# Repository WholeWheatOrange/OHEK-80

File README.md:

# OHEK-80
An analog hall effect keyboard using [Void Switches](https://github.com/riskable/void_switch) in the traditional 87-key tenkeyless layout.

# Roadmap
## Under Development
- PCB
## Planned Features
- Analog input
- Adjustable actuation point
- Rapid Trigger
- SOCD
- That Stupid Strap Attachment That Is A Trend In Hall Effect Keyboards

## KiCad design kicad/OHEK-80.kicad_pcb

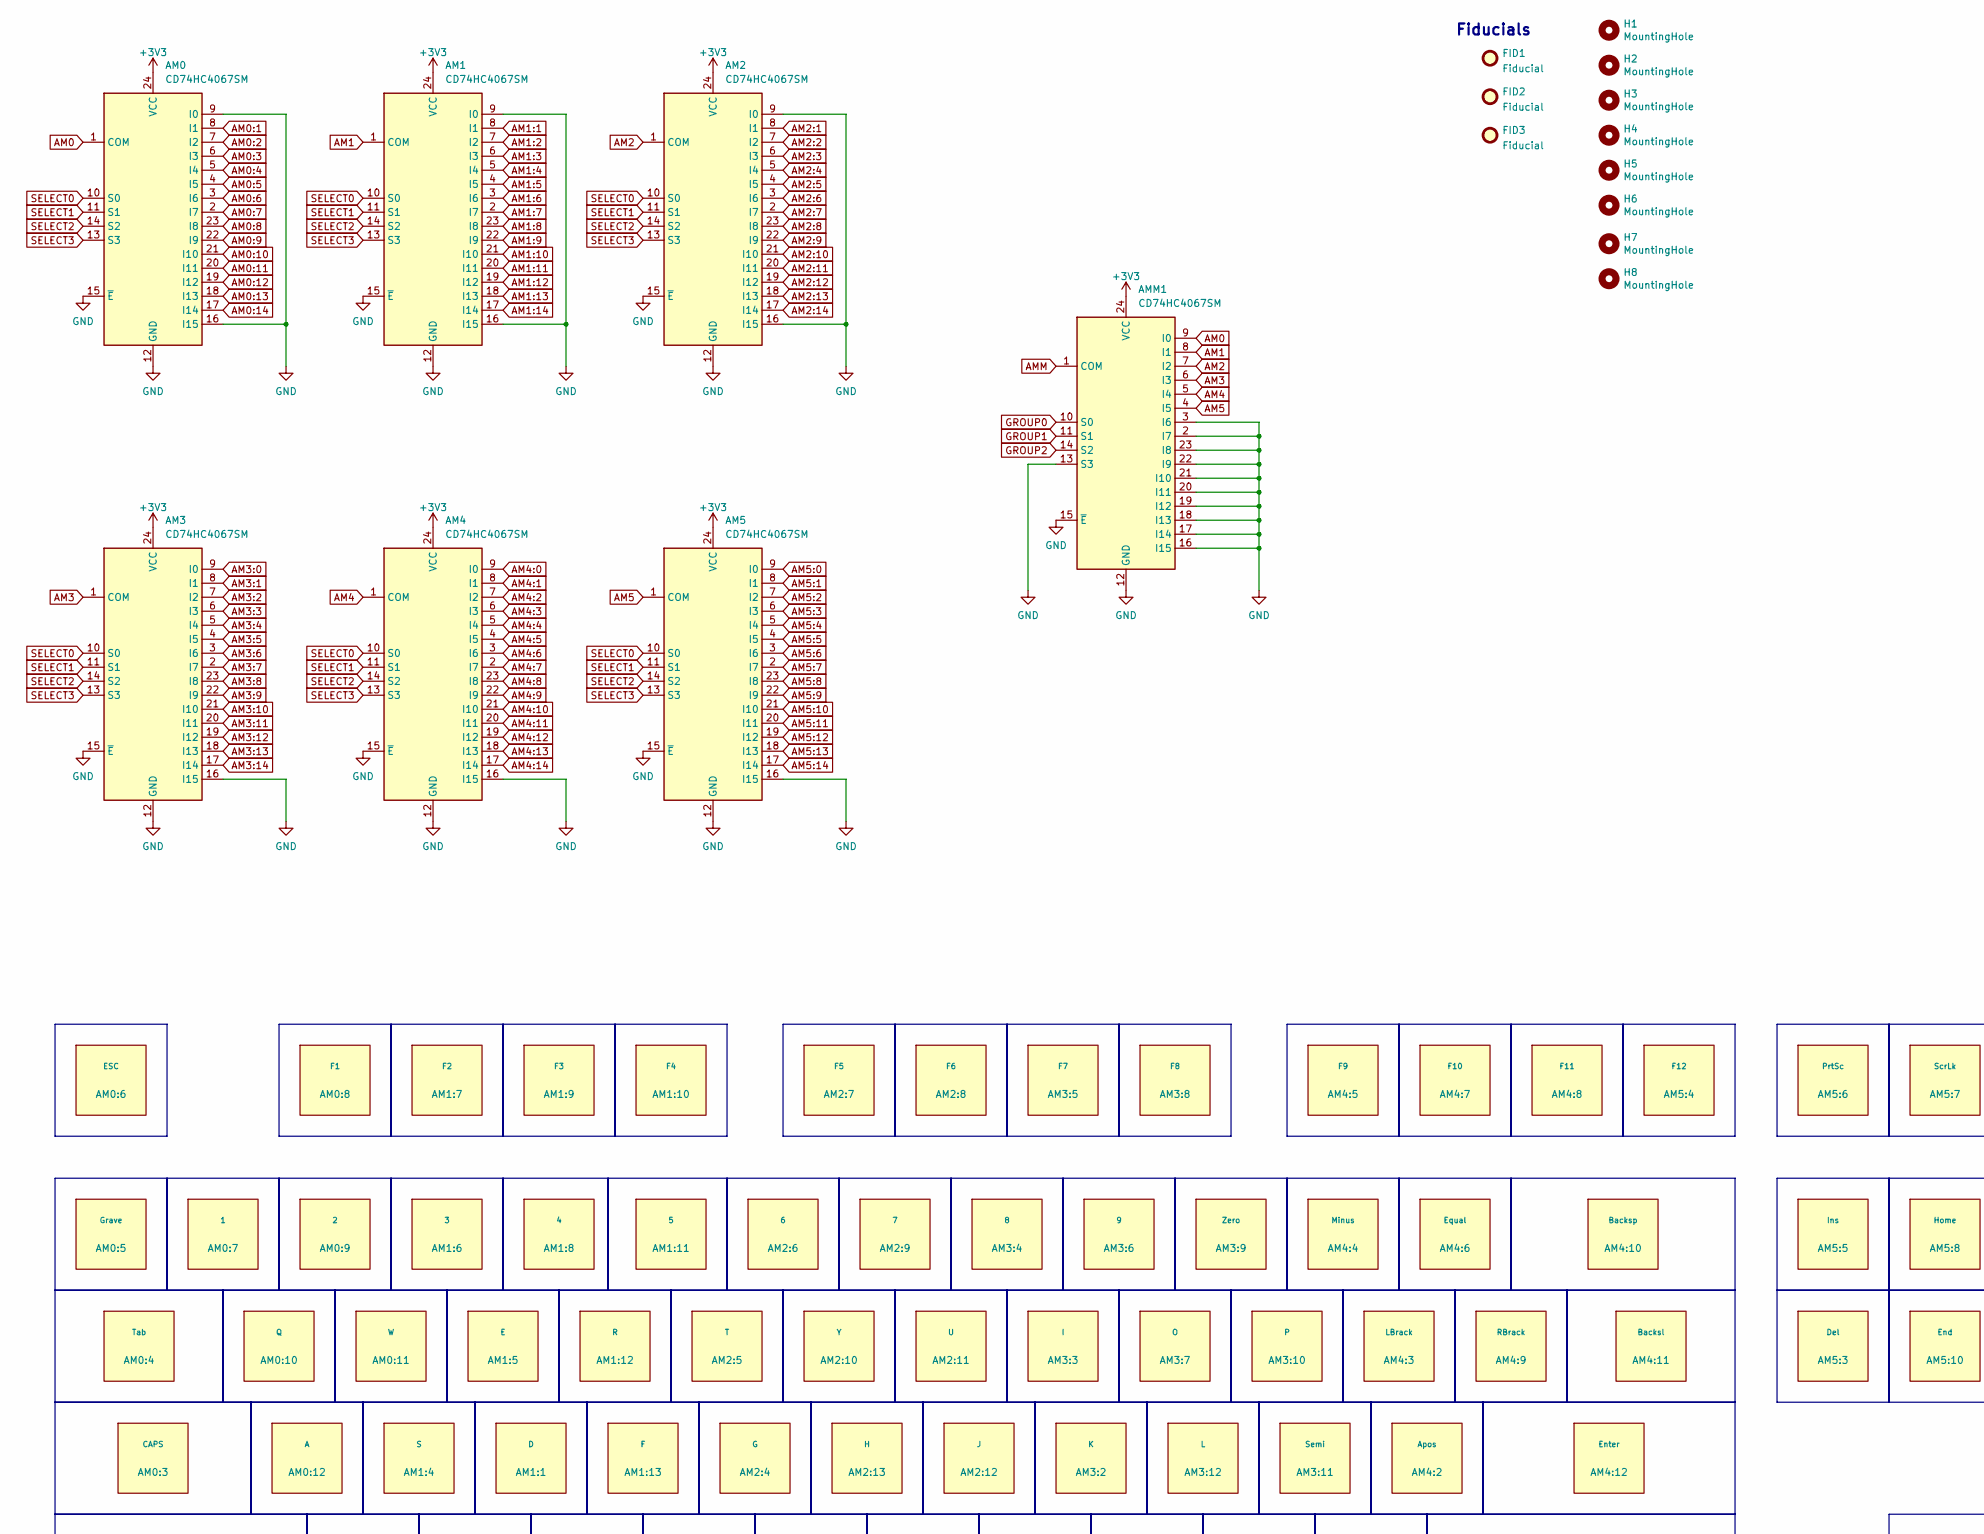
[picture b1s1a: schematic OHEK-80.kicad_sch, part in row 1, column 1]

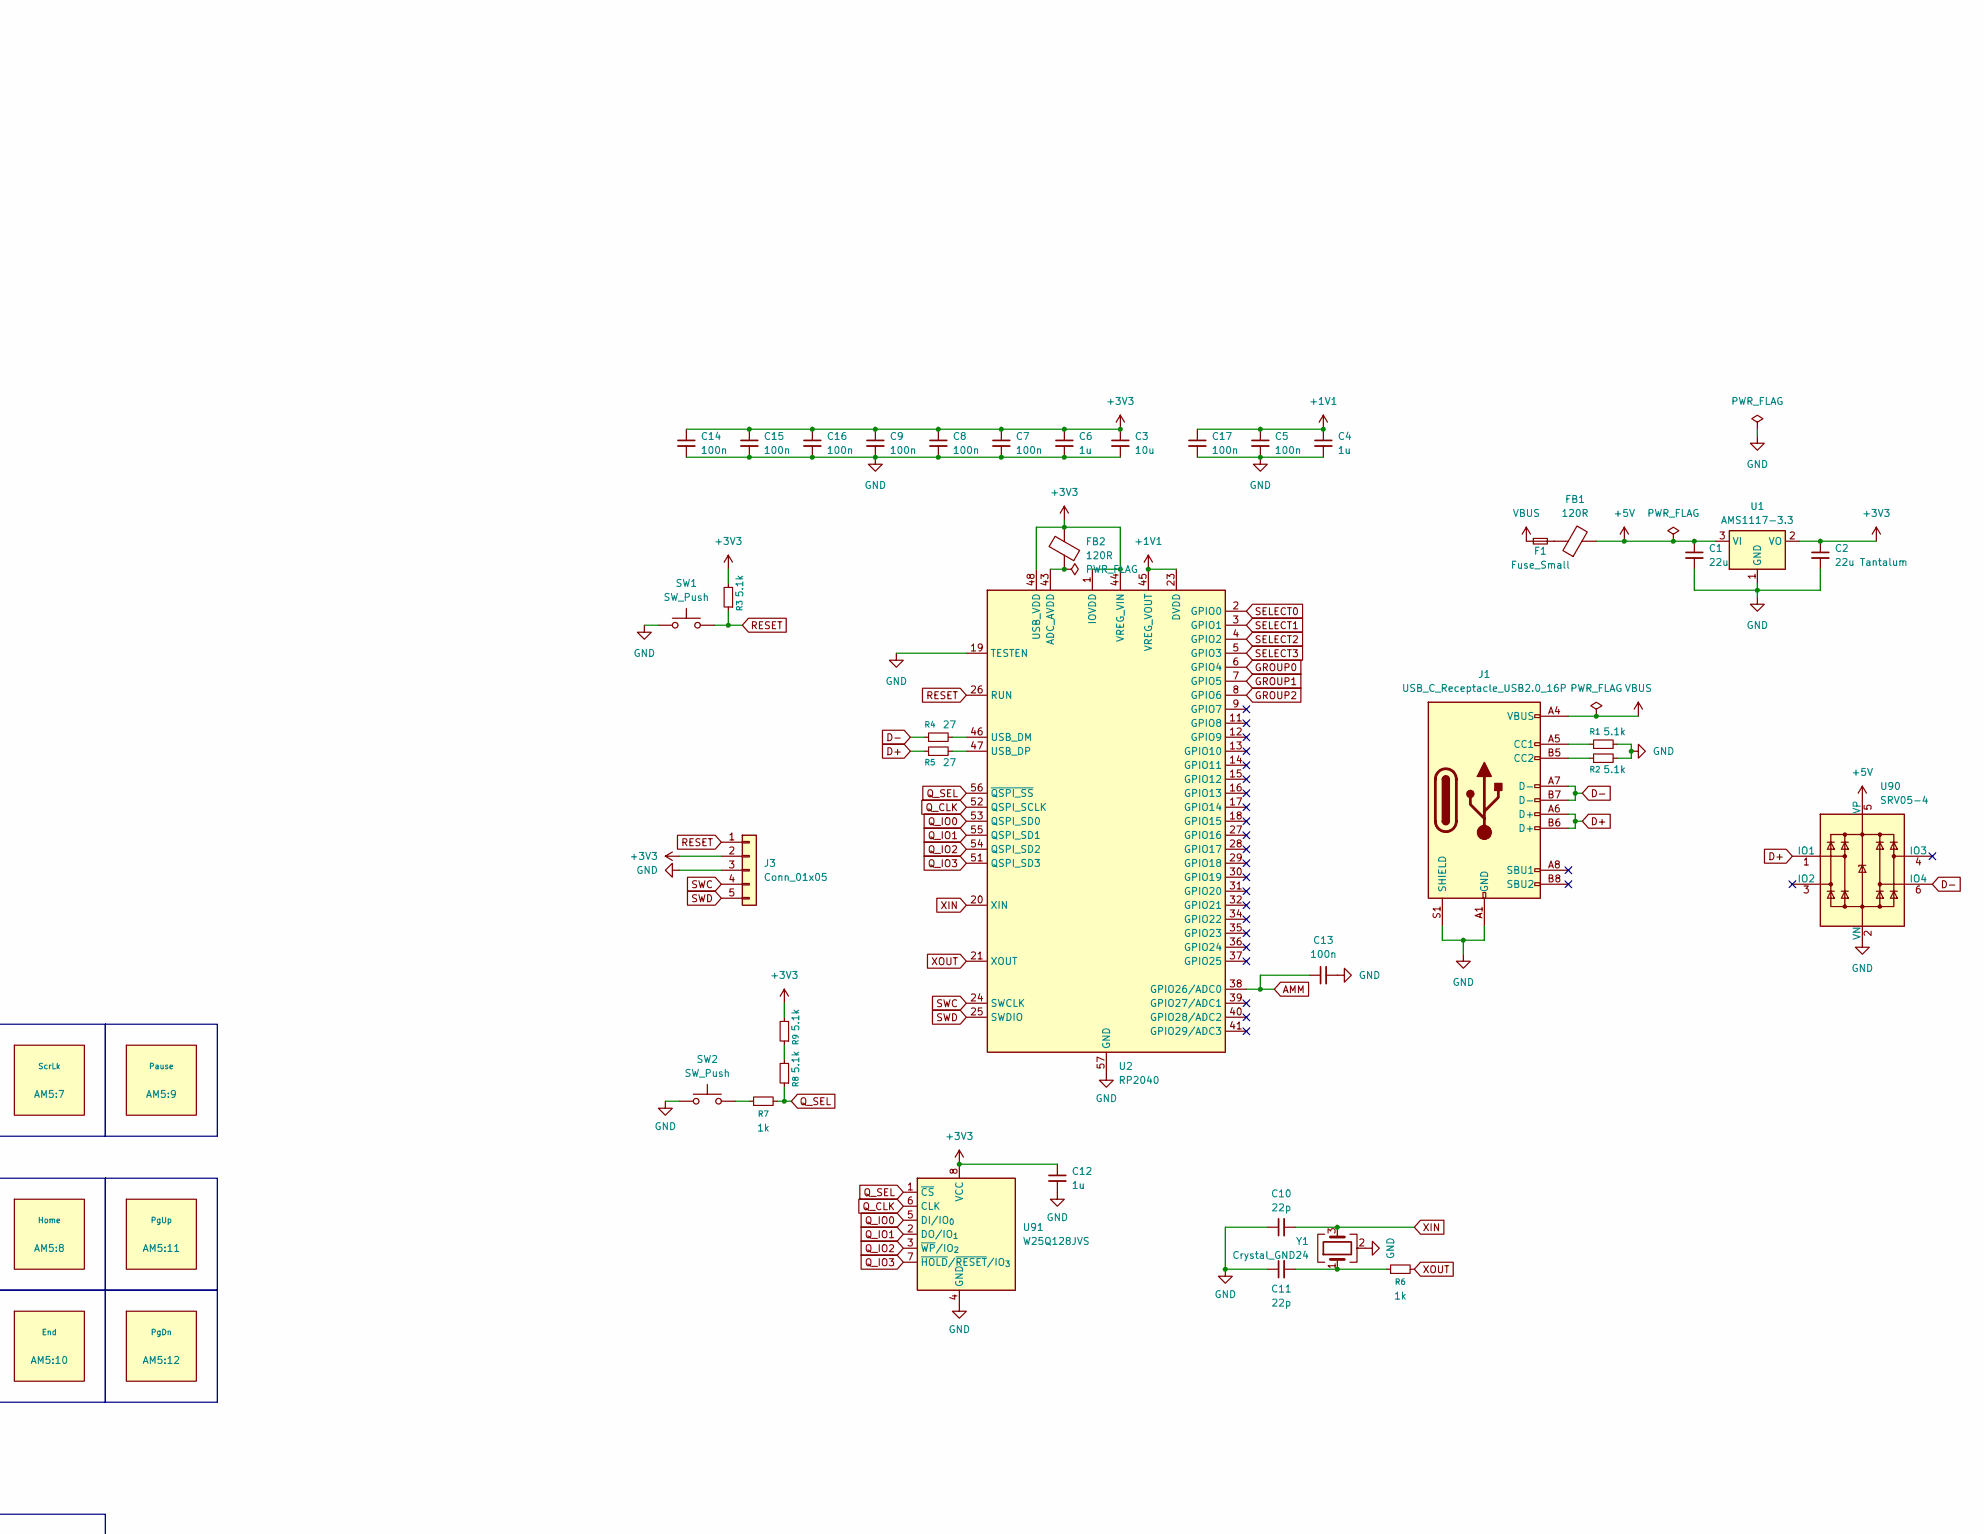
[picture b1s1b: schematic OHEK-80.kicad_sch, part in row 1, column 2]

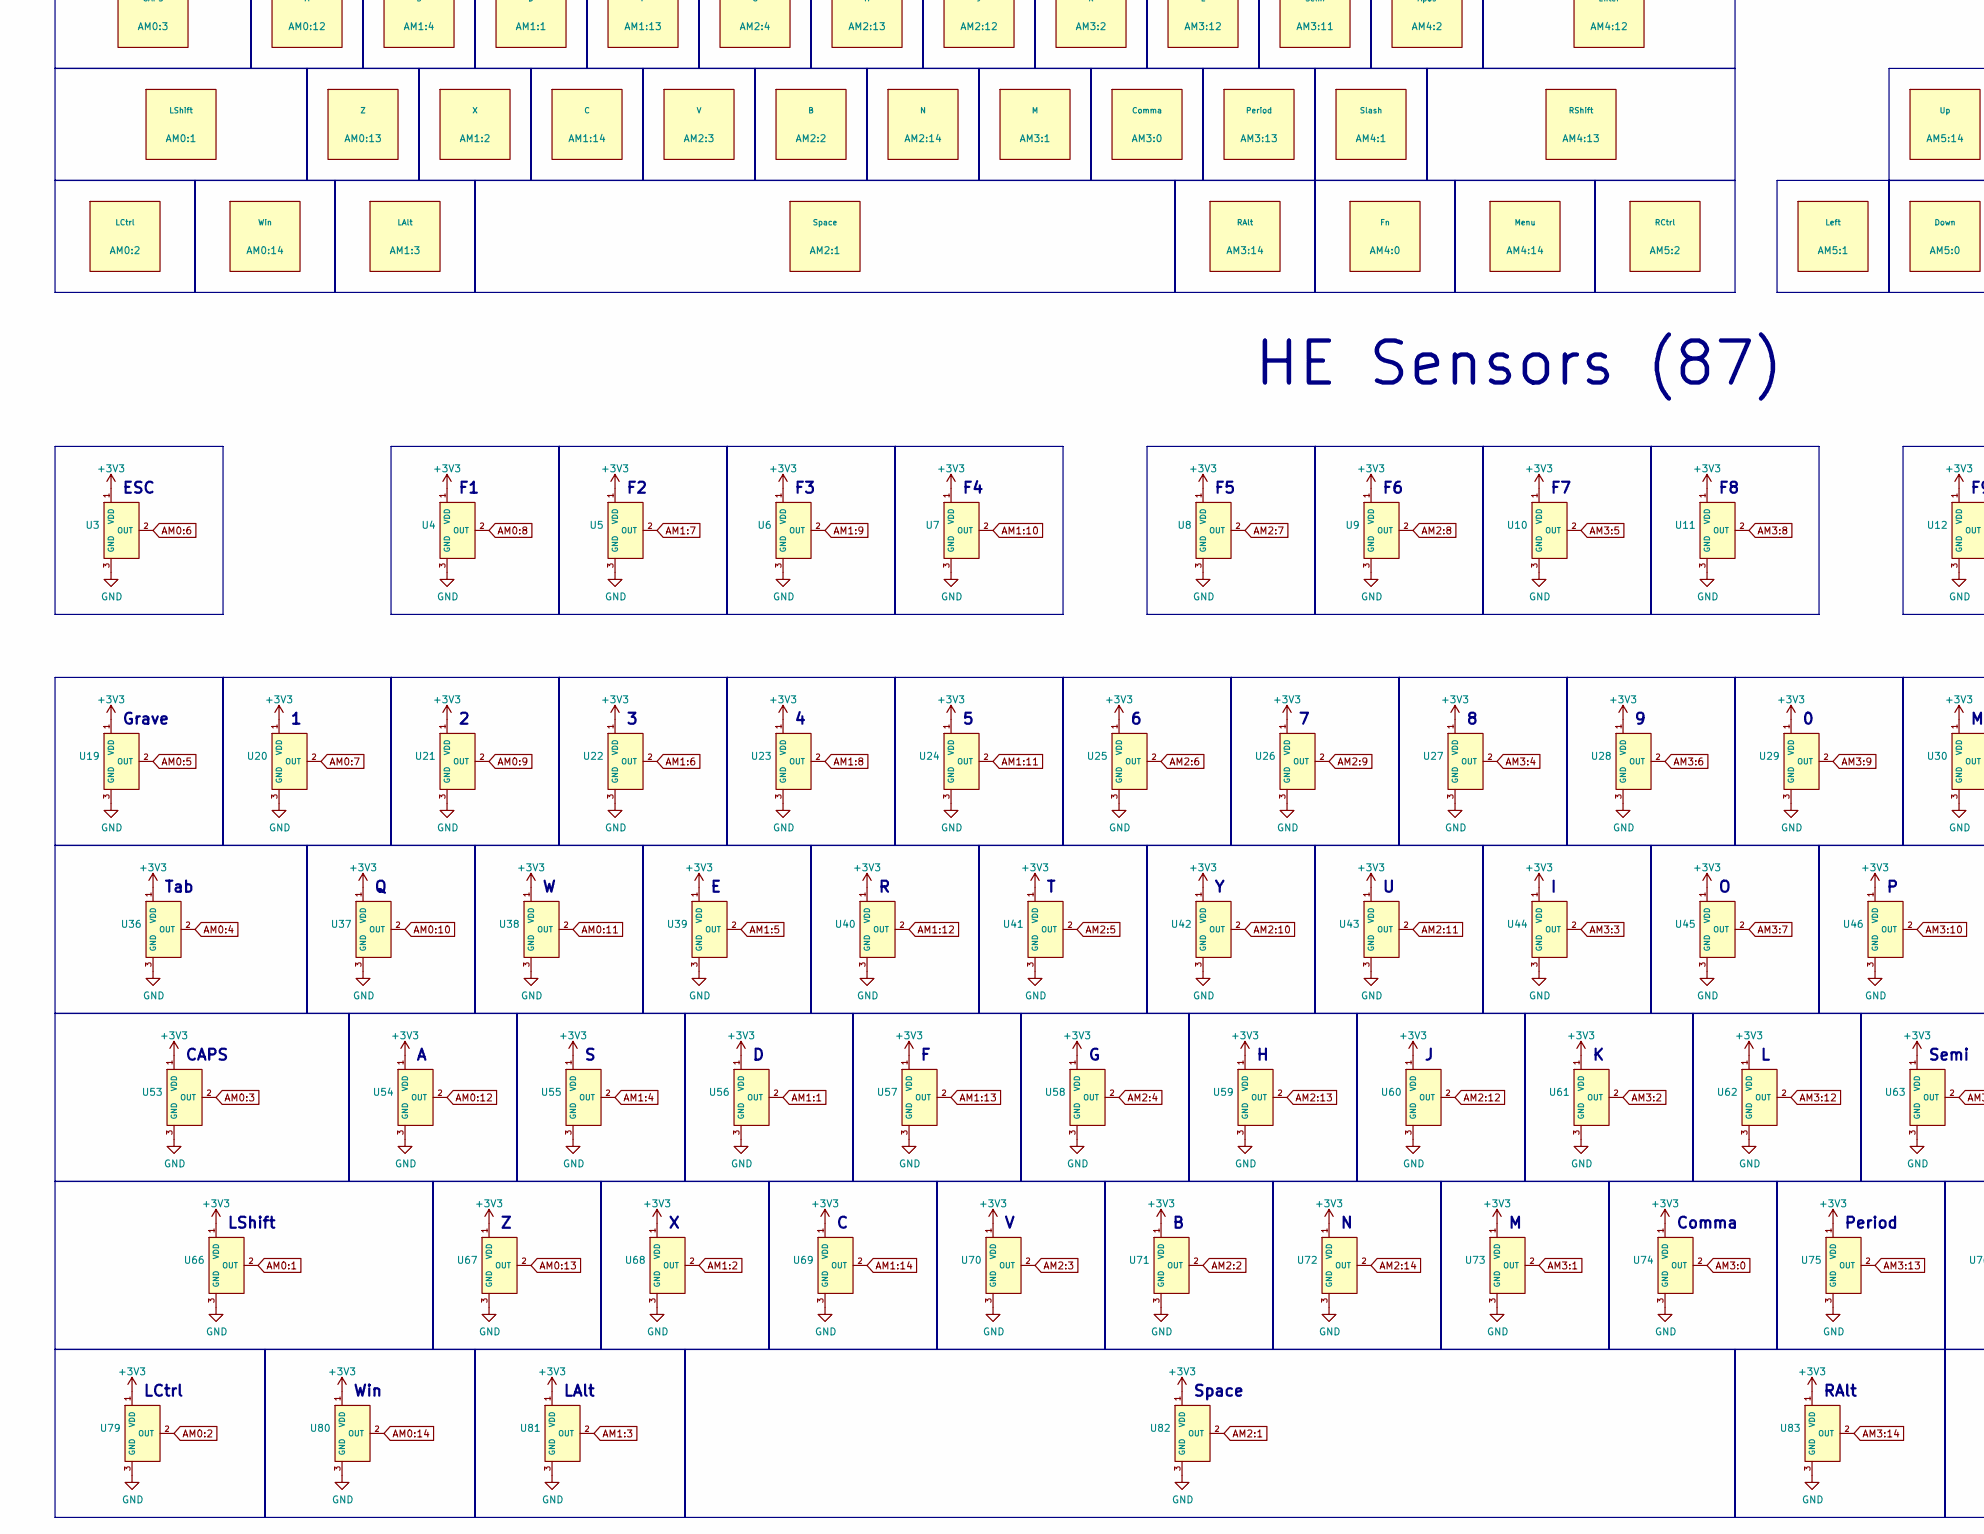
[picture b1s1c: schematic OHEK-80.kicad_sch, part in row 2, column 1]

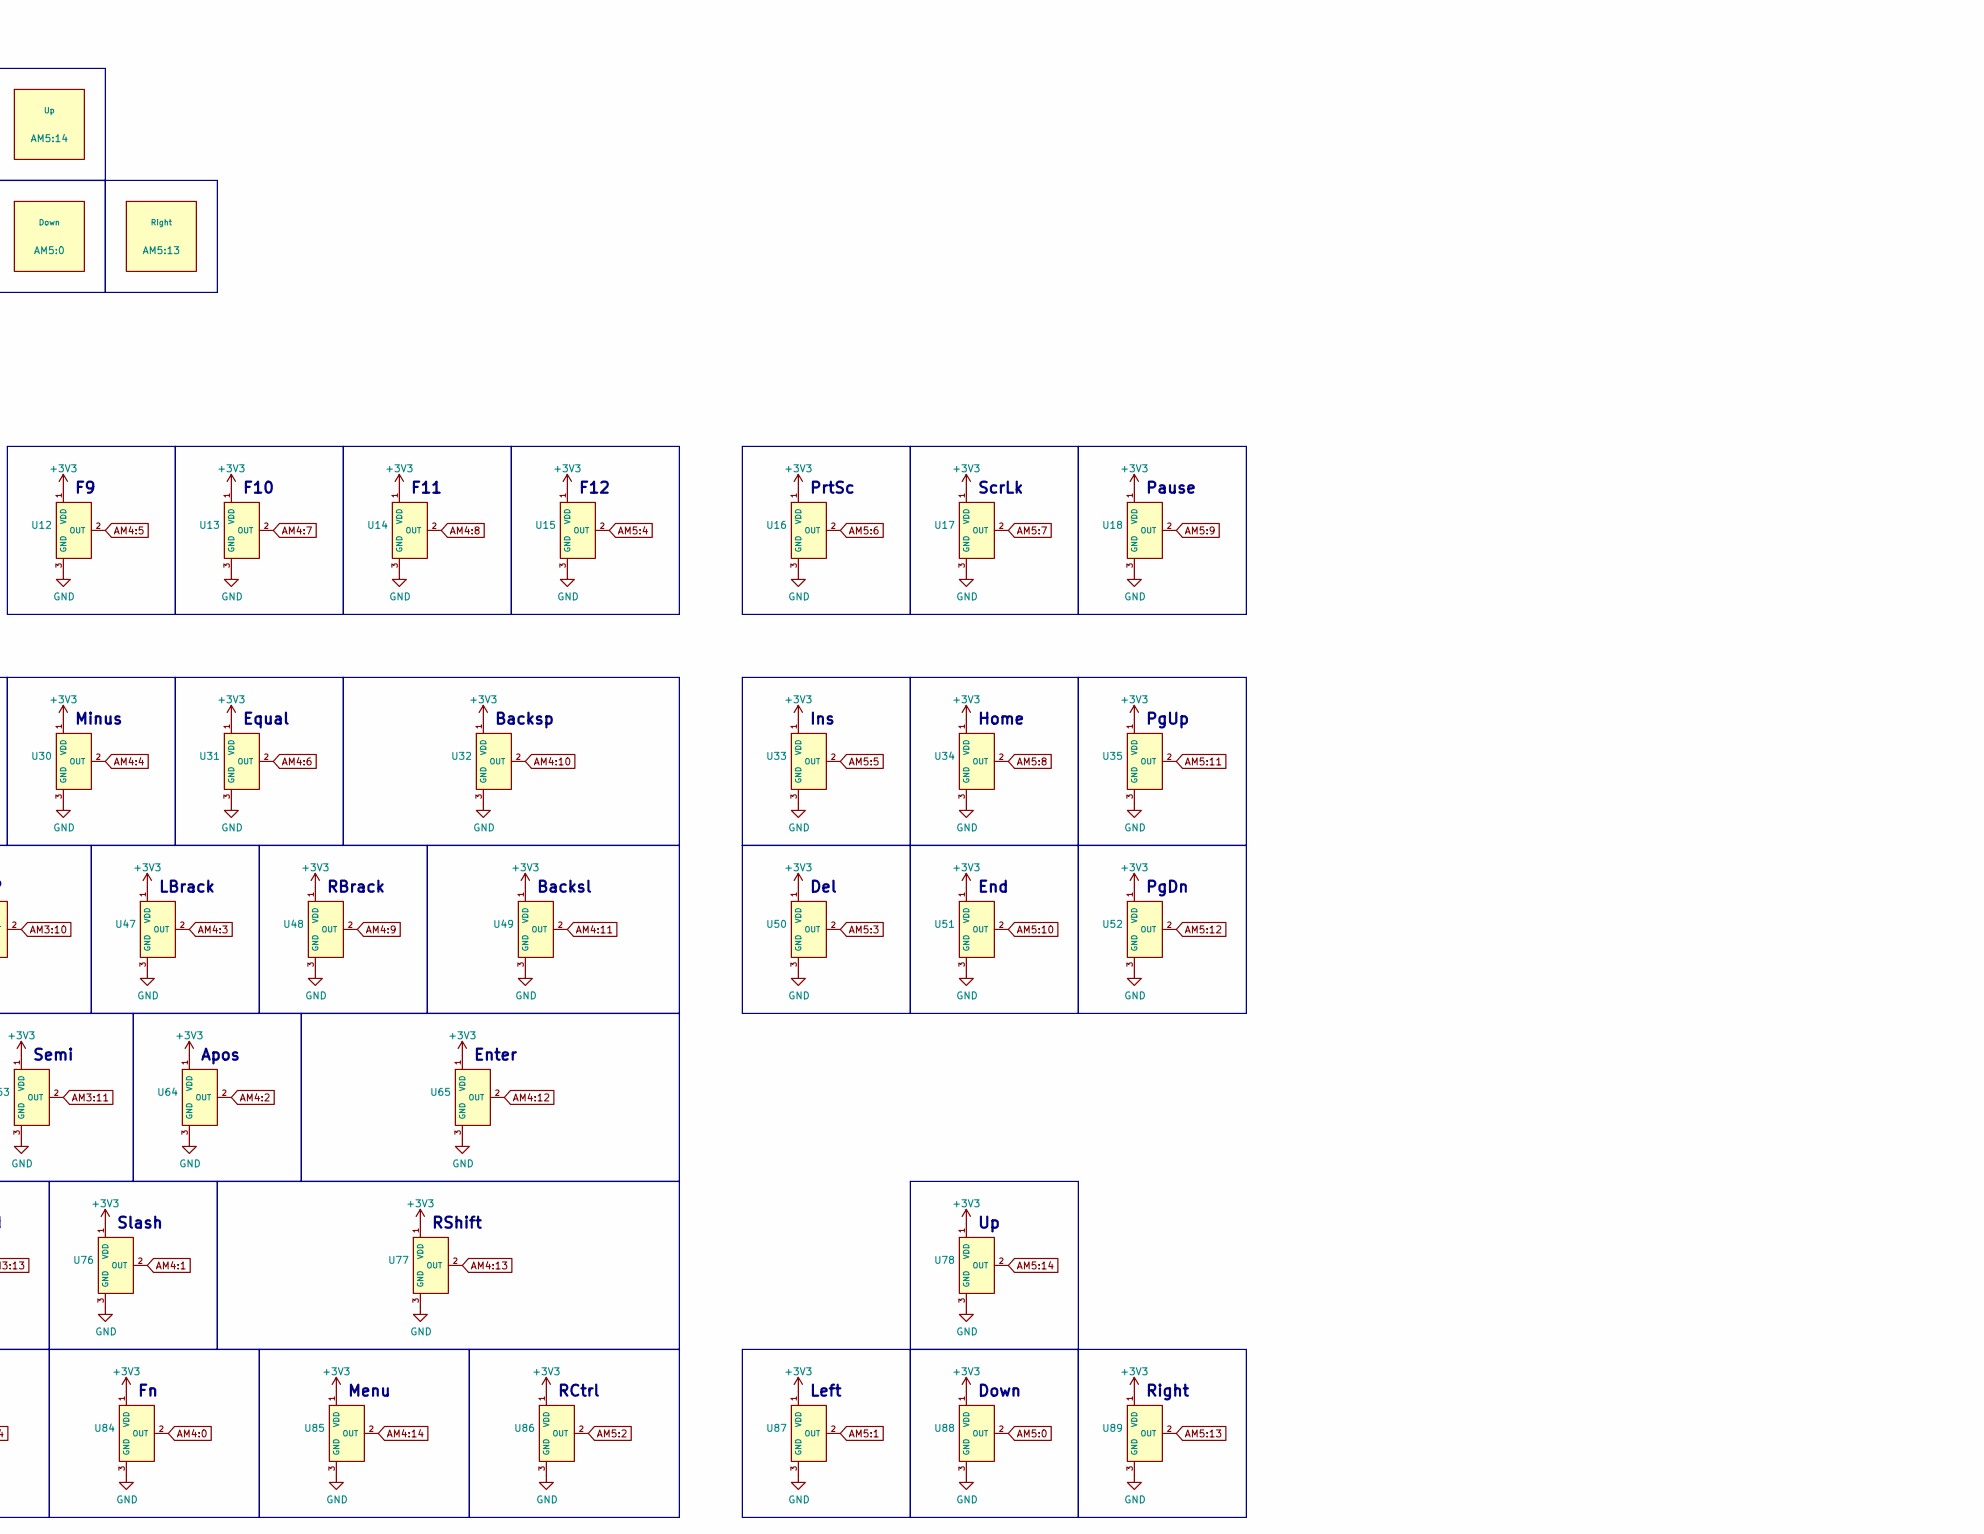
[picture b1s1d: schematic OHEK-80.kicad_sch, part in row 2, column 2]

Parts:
AM0, AM1, AM2, AM3, AM4, AM5: CD74HC4067SM; SSOP-24_5.3x8.2mm_P0.65mm; LCSC C98457
AM0:1: LShift; VoidSwitch_2.25u_SMD
AM0:2: LCtrl; VoidSwitch_1.25u_SMD
AM0:3: CAPS; VoidSwitch_1.75u_SMD
AM0:4: Tab; VoidSwitch_1.5u_SMD
AM0:5: Grave; VoidSwitch_1u_SMD
AM0:6: ESC; VoidSwitch_1u_SMD
AM0:7: 1; VoidSwitch_1u_SMD
AM0:8: F1; VoidSwitch_1u_SMD
AM0:9: 2; VoidSwitch_1u_SMD
AM0:10: Q; VoidSwitch_1u_SMD
AM0:11: W; VoidSwitch_1u_SMD
AM0:12: A; VoidSwitch_1u_SMD
AM0:13: Z; VoidSwitch_1u_SMD
AM0:14: Win; VoidSwitch_1.25u_SMD
AM1:1: D; VoidSwitch_1u_SMD
AM1:2: X; VoidSwitch_1u_SMD
AM1:3: LAlt; VoidSwitch_1.25u_SMD
AM1:4: S; VoidSwitch_1u_SMD
AM1:5: E; VoidSwitch_1u_SMD
AM1:6: 3; VoidSwitch_1u_SMD
AM1:7: F2; VoidSwitch_1u_SMD
AM1:8: 4; VoidSwitch_1u_SMD
AM1:9: F3; VoidSwitch_1u_SMD
AM1:10: F4; VoidSwitch_1u_SMD
AM1:11: 5; VoidSwitch_1u_SMD
AM1:12: R; VoidSwitch_1u_SMD
AM1:13: F; VoidSwitch_1u_SMD
AM1:14: C; VoidSwitch_1u_SMD
AM2:1: Space; VoidSwitch_6.25u_SMD
AM2:2: B; VoidSwitch_1u_SMD
AM2:3: V; VoidSwitch_1u_SMD
AM2:4: G; VoidSwitch_1u_SMD
AM2:5: T; VoidSwitch_1u_SMD
AM2:6: 6; VoidSwitch_1u_SMD
AM2:7: F5; VoidSwitch_1u_SMD
AM2:8: F6; VoidSwitch_1u_SMD
AM2:9: 7; VoidSwitch_1u_SMD
AM2:10: Y; VoidSwitch_1u_SMD
AM2:11: U; VoidSwitch_1u_SMD
AM2:12: J; VoidSwitch_1u_SMD
AM2:13: H; VoidSwitch_1u_SMD
AM2:14: N; VoidSwitch_1u_SMD
AM3:0: Comma; VoidSwitch_1u_SMD
AM3:1: M; VoidSwitch_1u_SMD
AM3:2: K; VoidSwitch_1u_SMD
AM3:3: I; VoidSwitch_1u_SMD
AM3:4: 8; VoidSwitch_1u_SMD
AM3:5: F7; VoidSwitch_1u_SMD
AM3:6: 9; VoidSwitch_1u_SMD
AM3:7: O; VoidSwitch_1u_SMD
AM3:8: F8; VoidSwitch_1u_SMD
AM3:9: Zero; VoidSwitch_1u_SMD
AM3:10: P; VoidSwitch_1u_SMD
AM3:11: Semi; VoidSwitch_1u_SMD
AM3:12: L; VoidSwitch_1u_SMD
AM3:13: Period; VoidSwitch_1u_SMD
AM3:14: RAlt; VoidSwitch_1.25u_SMD
AM4:0: Fn; VoidSwitch_1.25u_SMD
AM4:1: Slash; VoidSwitch_1u_SMD
AM4:2: Apos; VoidSwitch_1u_SMD
AM4:3: LBrack; VoidSwitch_1u_SMD
AM4:4: Minus; VoidSwitch_1u_SMD
AM4:5: F9; VoidSwitch_1u_SMD
AM4:6: Equal; VoidSwitch_1u_SMD
AM4:7: F10; VoidSwitch_1u_SMD
AM4:8: F11; VoidSwitch_1u_SMD
AM4:9: RBrack; VoidSwitch_1u_SMD
AM4:10: Backsp; VoidSwitch_2u_SMD
AM4:11: Backsl; VoidSwitch_1.5u_SMD
AM4:12: Enter; VoidSwitch_2.25u_SMD
AM4:13: RShift; VoidSwitch_2.75u_SMD
AM4:14: Menu; VoidSwitch_1.25u_SMD
AM5:0: Down; VoidSwitch_1u_SMD
AM5:1: Left; VoidSwitch_1u_SMD
AM5:2: RCtrl; VoidSwitch_1.25u_SMD
AM5:3: Del; VoidSwitch_1u_SMD
AM5:4: F12; VoidSwitch_1u_SMD
AM5:5: Ins; VoidSwitch_1u_SMD
AM5:6: PrtSc; VoidSwitch_1u_SMD
AM5:7: ScrLk; VoidSwitch_1u_SMD
AM5:8: Home; VoidSwitch_1u_SMD
AM5:9: Pause; VoidSwitch_1u_SMD
AM5:10: End; VoidSwitch_1u_SMD
AM5:11: PgUp; VoidSwitch_1u_SMD
AM5:12: PgDn; VoidSwitch_1u_SMD
AM5:13: Right; VoidSwitch_1u_SMD
AM5:14: Up; VoidSwitch_1u_SMD
AMM1: CD74HC4067SM; SSOP-24_5.3x8.2mm_P0.65mm; LCSC C98457
C1: 22u; C_0805_2012Metric
C2: 22u Tantalum; C_0805_2012Metric; LCSC C1954754
C3: 10u; C_0805_2012Metric
C4, C6, C12: 1u; C_0805_2012Metric
C5, C7, C8, C9, C13, C14, C15, C16, C17: 100n; C_0805_2012Metric
C10, C11: 22p; C_0805_2012Metric
F1: Fuse_Small; Fuse_1206_3216Metric; LCSC C49318386
FB1, FB2: 120R; L_0805_2012Metric; LCSC C79382
FID1, FID2, FID3: Fiducial; Fiducial_1mm_Mask2mm
H1, H2, H3, H4, H5, H6, H7, H8: MountingHole; MountingHole_3.2mm_M3_Pad
J1: USB_C_Receptacle_USB2.0_16P; USB_C_Receptacle_HRO_TYPE-C-31-M-12; LCSC C165948
J3: Conn_01x05; JST_PH_S5B-PH-K_1x05_P2.00mm_Horizontal; LCSC C157923
R1, R2, R3, R8, R9: 5.1k; R_0805_2012Metric
R4, R5: 27; R_0805_2012Metric
R6, R7: 1k; R_0805_2012Metric
SW1, SW2: SW_Push; SW_SPST_TL3342; LCSC C318884
U1: AMS1117-3.3; SOT-223-3_TabPin2; LCSC C6186
U2: RP2040; QFN-56-1EP_7x7mm_P0.4mm_EP3.2x3.2mm; LCSC C2040
U3, U4, U5, U6, U7, U8, U9, U10, U11, U12, U13, U14, U15, U16, U17, U18, U19, U20, U21, U22, U23, U24, U25, U26, U27, U28, U29, U30, U31, U32, U33, U34, U35, U36, U37, U38, U39, U40, U41, U42, U43, U44, U45, U46, U47, U48, U49, U50, U51, U52, U53, U54, U55, U56, U57, U58, U59, U60, U61, U62, U63, U64, U65, U66, U67, U68, U69, U70, U71, U72, U73, U74, U75, U76, U77, U78, U79, U80, U81, U82, U83, U84, U85, U86, U87, U88, U89: GH39FKSW; SOT-23; MPN GH39FKSW; LCSC Part C266230
U90: SRV05-4; SOT-23-6; LCSC C7420376
U91: W25Q128JVS; SOIC-8_5.3x5.3mm_P1.27mm; LCSC C97521
Y1: Crystal_GND24; Crystal_SMD_3225-4Pin_3.2x2.5mm; LCSC C20625731

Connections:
+1V1: C4.1, C5.1, C17.1, U2.23 (DVDD), U2.45 (VREG_VOUT), U2.50 (DVDD)
+3V3: AM0.24 (VCC), AM1.24 (VCC), AM2.24 (VCC), AM3.24 (VCC), AM4.24 (VCC), AM5.24 (VCC), AMM1.24 (VCC), C2.1, C3.1, C6.1, C7.1, C8.1, C9.1, C12.1, C14.1, C15.1, C16.1, FB2.2, J3.2, R3.2, R9.2, U1.2 (VO), U2.1 (IOVDD), U2.10 (IOVDD), U2.22 (IOVDD), U2.33 (IOVDD), U2.42 (IOVDD), U2.44 (VREG_VIN), U2.48 (USB_VDD), U2.49 (IOVDD), U3.1 (VDD), U4.1 (VDD), U5.1 (VDD), U6.1 (VDD), U7.1 (VDD), U8.1 (VDD), U9.1 (VDD), U10.1 (VDD), U11.1 (VDD), U12.1 (VDD), U13.1 (VDD), U14.1 (VDD), U15.1 (VDD), U16.1 (VDD), U17.1 (VDD), U18.1 (VDD), U19.1 (VDD), U20.1 (VDD), U21.1 (VDD), U22.1 (VDD), U23.1 (VDD), U24.1 (VDD), U25.1 (VDD), U26.1 (VDD), U27.1 (VDD), U28.1 (VDD), U29.1 (VDD), U30.1 (VDD), U31.1 (VDD), U32.1 (VDD), U33.1 (VDD), U34.1 (VDD), U35.1 (VDD), U36.1 (VDD), U37.1 (VDD), U38.1 (VDD), U39.1 (VDD), U40.1 (VDD), U41.1 (VDD), U42.1 (VDD), U43.1 (VDD), U44.1 (VDD), U45.1 (VDD), U46.1 (VDD), U47.1 (VDD), U48.1 (VDD), U49.1 (VDD), U50.1 (VDD), U51.1 (VDD), U52.1 (VDD), U53.1 (VDD), U54.1 (VDD), U55.1 (VDD), U56.1 (VDD), U57.1 (VDD), U58.1 (VDD), U59.1 (VDD), U60.1 (VDD), U61.1 (VDD), U62.1 (VDD), U63.1 (VDD), U64.1 (VDD), U65.1 (VDD), U66.1 (VDD), U67.1 (VDD), U68.1 (VDD), U69.1 (VDD), U70.1 (VDD), U71.1 (VDD), U72.1 (VDD), U73.1 (VDD), U74.1 (VDD), U75.1 (VDD), U76.1 (VDD), U77.1 (VDD), U78.1 (VDD), U79.1 (VDD), U80.1 (VDD), U81.1 (VDD), U82.1 (VDD), U83.1 (VDD), U84.1 (VDD), U85.1 (VDD), U86.1 (VDD), U87.1 (VDD), U88.1 (VDD), U89.1 (VDD), U91.8 (VCC)
+5V: C1.1, FB1.2, U1.3 (VI), U90.5 (VP)
AM0: AM0.1 (COM), AMM1.9 (I0)
AM0:1: AM0.8 (I1), U66.2 (OUT)
AM0:2: AM0.7 (I2), U79.2 (OUT)
AM0:3: AM0.6 (I3), U53.2 (OUT)
AM0:4: AM0.5 (I4), U36.2 (OUT)
AM0:5: AM0.4 (I5), U19.2 (OUT)
AM0:6: AM0.3 (I6), U3.2 (OUT)
AM0:7: AM0.2 (I7), U20.2 (OUT)
AM0:8: AM0.23 (I8), U4.2 (OUT)
AM0:9: AM0.22 (I9), U21.2 (OUT)
AM0:10: AM0.21 (I10), U37.2 (OUT)
AM0:11: AM0.20 (I11), U38.2 (OUT)
AM0:12: AM0.19 (I12), U54.2 (OUT)
AM0:13: AM0.18 (I13), U67.2 (OUT)
AM0:14: AM0.17 (I14), U80.2 (OUT)
AM1: AM1.1 (COM), AMM1.8 (I1)
AM1:1: AM1.8 (I1), U56.2 (OUT)
AM1:2: AM1.7 (I2), U68.2 (OUT)
AM1:3: AM1.6 (I3), U81.2 (OUT)
AM1:4: AM1.5 (I4), U55.2 (OUT)
AM1:5: AM1.4 (I5), U39.2 (OUT)
AM1:6: AM1.3 (I6), U22.2 (OUT)
AM1:7: AM1.2 (I7), U5.2 (OUT)
AM1:8: AM1.23 (I8), U23.2 (OUT)
AM1:9: AM1.22 (I9), U6.2 (OUT)
AM1:10: AM1.21 (I10), U7.2 (OUT)
AM1:11: AM1.20 (I11), U24.2 (OUT)
AM1:12: AM1.19 (I12), U40.2 (OUT)
AM1:13: AM1.18 (I13), U57.2 (OUT)
AM1:14: AM1.17 (I14), U69.2 (OUT)
AM2: AM2.1 (COM), AMM1.7 (I2)
AM2:1: AM2.8 (I1), U82.2 (OUT)
AM2:2: AM2.7 (I2), U71.2 (OUT)
AM2:3: AM2.6 (I3), U70.2 (OUT)
AM2:4: AM2.5 (I4), U58.2 (OUT)
AM2:5: AM2.4 (I5), U41.2 (OUT)
AM2:6: AM2.3 (I6), U25.2 (OUT)
AM2:7: AM2.2 (I7), U8.2 (OUT)
AM2:8: AM2.23 (I8), U9.2 (OUT)
AM2:9: AM2.22 (I9), U26.2 (OUT)
AM2:10: AM2.21 (I10), U42.2 (OUT)
AM2:11: AM2.20 (I11), U43.2 (OUT)
AM2:12: AM2.19 (I12), U60.2 (OUT)
AM2:13: AM2.18 (I13), U59.2 (OUT)
AM2:14: AM2.17 (I14), U72.2 (OUT)
AM3: AM3.1 (COM), AMM1.6 (I3)
AM3:0: AM3.9 (I0), U74.2 (OUT)
AM3:1: AM3.8 (I1), U73.2 (OUT)
AM3:2: AM3.7 (I2), U61.2 (OUT)
AM3:3: AM3.6 (I3), U44.2 (OUT)
AM3:4: AM3.5 (I4), U27.2 (OUT)
AM3:5: AM3.4 (I5), U10.2 (OUT)
AM3:6: AM3.3 (I6), U28.2 (OUT)
AM3:7: AM3.2 (I7), U45.2 (OUT)
AM3:8: AM3.23 (I8), U11.2 (OUT)
AM3:9: AM3.22 (I9), U29.2 (OUT)
AM3:10: AM3.21 (I10), U46.2 (OUT)
AM3:11: AM3.20 (I11), U63.2 (OUT)
AM3:12: AM3.19 (I12), U62.2 (OUT)
AM3:13: AM3.18 (I13), U75.2 (OUT)
AM3:14: AM3.17 (I14), U83.2 (OUT)
AM4: AM4.1 (COM), AMM1.5 (I4)
AM4:0: AM4.9 (I0), U84.2 (OUT)
AM4:1: AM4.8 (I1), U76.2 (OUT)
AM4:2: AM4.7 (I2), U64.2 (OUT)
AM4:3: AM4.6 (I3), U47.2 (OUT)
AM4:4: AM4.5 (I4), U30.2 (OUT)
AM4:5: AM4.4 (I5), U12.2 (OUT)
AM4:6: AM4.3 (I6), U31.2 (OUT)
AM4:7: AM4.2 (I7), U13.2 (OUT)
AM4:8: AM4.23 (I8), U14.2 (OUT)
AM4:9: AM4.22 (I9), U48.2 (OUT)
AM4:10: AM4.21 (I10), U32.2 (OUT)
AM4:11: AM4.20 (I11), U49.2 (OUT)
AM4:12: AM4.19 (I12), U65.2 (OUT)
AM4:13: AM4.18 (I13), U77.2 (OUT)
AM4:14: AM4.17 (I14), U85.2 (OUT)
AM5: AM5.1 (COM), AMM1.4 (I5)
AM5:0: AM5.9 (I0), U88.2 (OUT)
AM5:1: AM5.8 (I1), U87.2 (OUT)
AM5:2: AM5.7 (I2), U86.2 (OUT)
AM5:3: AM5.6 (I3), U50.2 (OUT)
AM5:4: AM5.5 (I4), U15.2 (OUT)
AM5:5: AM5.4 (I5), U33.2 (OUT)
AM5:6: AM5.3 (I6), U16.2 (OUT)
AM5:7: AM5.2 (I7), U17.2 (OUT)
AM5:8: AM5.23 (I8), U34.2 (OUT)
AM5:9: AM5.22 (I9), U18.2 (OUT)
AM5:10: AM5.21 (I10), U51.2 (OUT)
AM5:11: AM5.20 (I11), U35.2 (OUT)
AM5:12: AM5.19 (I12), U52.2 (OUT)
AM5:13: AM5.18 (I13), U89.2 (OUT)
AM5:14: AM5.17 (I14), U78.2 (OUT)
AMM: AMM1.1 (COM), C13.1, U2.38 (GPIO26/ADC0)
D+: J1.A6 (D+), J1.B6 (D+), R5.1, U90.1 (IO1)
D-: J1.A7 (D-), J1.B7 (D-), R4.1, U90.6 (IO4)
GND: AM0.9 (I0), AM0.12 (GND), AM0.15 (~E), AM0.16 (I15), AM1.9 (I0), AM1.12 (GND), AM1.15 (~E), AM1.16 (I15), AM2.9 (I0), AM2.12 (GND), AM2.15 (~E), AM2.16 (I15), AM3.12 (GND), AM3.15 (~E), AM3.16 (I15), AM4.12 (GND), AM4.15 (~E), AM4.16 (I15), AM5.12 (GND), AM5.15 (~E), AM5.16 (I15), AMM1.2 (I7), AMM1.3 (I6), AMM1.12 (GND), AMM1.13 (S3), AMM1.15 (~E), AMM1.16 (I15), AMM1.17 (I14), AMM1.18 (I13), AMM1.19 (I12), AMM1.20 (I11), AMM1.21 (I10), AMM1.22 (I9), AMM1.23 (I8), C1.2, C2.2, C3.2, C4.2, C5.2, C6.2, C7.2, C8.2, C9.2, C10.1, C11.1, C12.2, C13.2, C14.2, C15.2, C16.2, C17.2, J1.A1 (GND), J1.A12 (GND), J1.B1 (GND), J1.B12 (GND), J1.S1 (SHIELD), J3.3, R1.2, R2.2, SW1.1, SW2.1, U1.1 (GND), U2.19 (TESTEN), U2.57 (GND), U3.3 (GND), U4.3 (GND), U5.3 (GND), U6.3 (GND), U7.3 (GND), U8.3 (GND), U9.3 (GND), U10.3 (GND), U11.3 (GND), U12.3 (GND), U13.3 (GND), U14.3 (GND), U15.3 (GND), U16.3 (GND), U17.3 (GND), U18.3 (GND), U19.3 (GND), U20.3 (GND), U21.3 (GND), U22.3 (GND), U23.3 (GND), U24.3 (GND), U25.3 (GND), U26.3 (GND), U27.3 (GND), U28.3 (GND), U29.3 (GND), U30.3 (GND), U31.3 (GND), U32.3 (GND), U33.3 (GND), U34.3 (GND), U35.3 (GND), U36.3 (GND), U37.3 (GND), U38.3 (GND), U39.3 (GND), U40.3 (GND), U41.3 (GND), U42.3 (GND), U43.3 (GND), U44.3 (GND), U45.3 (GND), U46.3 (GND), U47.3 (GND), U48.3 (GND), U49.3 (GND), U50.3 (GND), U51.3 (GND), U52.3 (GND), U53.3 (GND), U54.3 (GND), U55.3 (GND), U56.3 (GND), U57.3 (GND), U58.3 (GND), U59.3 (GND), U60.3 (GND), U61.3 (GND), U62.3 (GND), U63.3 (GND), U64.3 (GND), U65.3 (GND), U66.3 (GND), U67.3 (GND), U68.3 (GND), U69.3 (GND), U70.3 (GND), U71.3 (GND), U72.3 (GND), U73.3 (GND), U74.3 (GND), U75.3 (GND), U76.3 (GND), U77.3 (GND), U78.3 (GND), U79.3 (GND), U80.3 (GND), U81.3 (GND), U82.3 (GND), U83.3 (GND), U84.3 (GND), U85.3 (GND), U86.3 (GND), U87.3 (GND), U88.3 (GND), U89.3 (GND), U90.2 (VN), U91.4 (GND), Y1.2 (G), Y1.4 (G)
GROUP0: AMM1.10 (S0), U2.6 (GPIO4)
GROUP1: AMM1.11 (S1), U2.7 (GPIO5)
GROUP2: AMM1.14 (S2), U2.8 (GPIO6)
unnamed: C11.2, R6.1, Y1.1
unnamed: F1.2, FB1.1
unnamed: J1.A5 (CC1), R1.1
unnamed: J1.B5 (CC2), R2.1
unnamed: R7.1, SW2.2
unnamed: R8.2, R9.1
unnamed: FB2.1, U2.43 (ADC_AVDD)
unnamed: R4.2, U2.46 (USB_DM)
unnamed: R5.2, U2.47 (USB_DP)
Q_CLK: U2.52 (QSPI_SCLK), U91.6 (CLK)
Q_IO0: U2.53 (QSPI_SD0), U91.5 (DI/IO_{0})
Q_IO1: U2.55 (QSPI_SD1), U91.2 (DO/IO_{1})
Q_IO2: U2.54 (QSPI_SD2), U91.3 (~WP/IO_{2})
Q_IO3: U2.51 (QSPI_SD3), U91.7 (~HOLD/~RESET/IO_{3})
Q_SEL: R7.2, R8.1, U2.56 (~QSPI_SS), U91.1 (~CS)
RESET: J3.1, R3.1, SW1.2, U2.26 (RUN)
SELECT0: AM0.10 (S0), AM1.10 (S0), AM2.10 (S0), AM3.10 (S0), AM4.10 (S0), AM5.10 (S0), U2.2 (GPIO0)
SELECT1: AM0.11 (S1), AM1.11 (S1), AM2.11 (S1), AM3.11 (S1), AM4.11 (S1), AM5.11 (S1), U2.3 (GPIO1)
SELECT2: AM0.14 (S2), AM1.14 (S2), AM2.14 (S2), AM3.14 (S2), AM4.14 (S2), AM5.14 (S2), U2.4 (GPIO2)
SELECT3: AM0.13 (S3), AM1.13 (S3), AM2.13 (S3), AM3.13 (S3), AM4.13 (S3), AM5.13 (S3), U2.5 (GPIO3)
SWC: J3.4, U2.24 (SWCLK)
SWD: J3.5, U2.25 (SWDIO)
VBUS: F1.1, J1.A4 (VBUS), J1.A9 (VBUS), J1.B4 (VBUS), J1.B9 (VBUS)
XIN: C10.2, U2.20 (XIN), Y1.3
XOUT: R6.2, U2.21 (XOUT)

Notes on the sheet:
Home
RAlt
PgUp
End
ScrLk
Right
RBrack
Del
Slash
Backsp
LAlt
Ins
Enter
Semi
Left
LCtrl
F10
Grave
Equal
PrtSc
Down
HE Sensors (87)
Menu
Comma
Space
Tab
Pause
CAPS
RCtrl
F12
Apos
F11
Backsl
Period
LShift
LBrack
Minus
Fiducials
ESC
PgDn

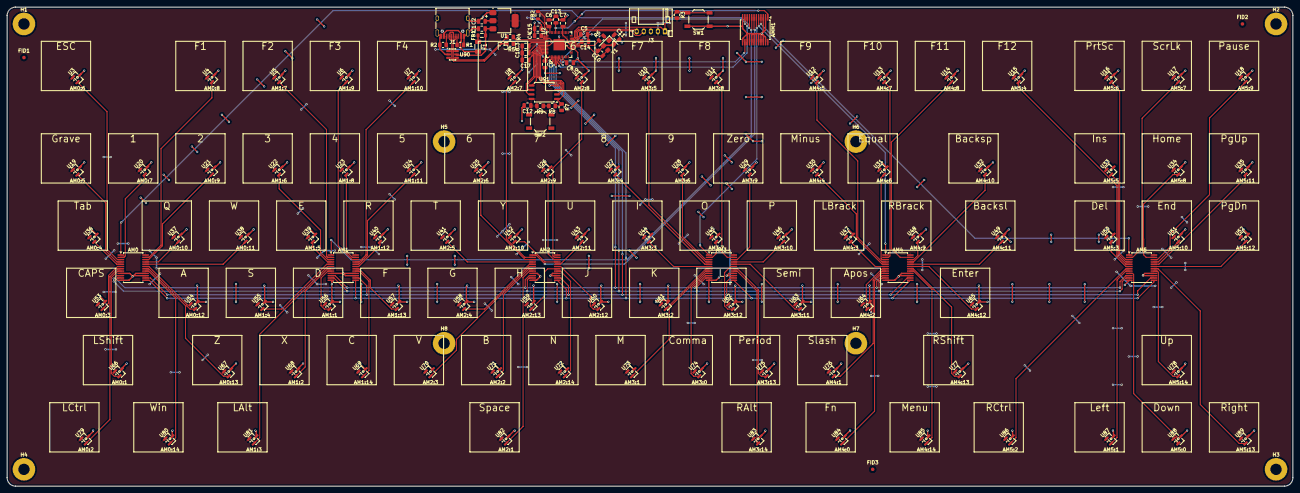
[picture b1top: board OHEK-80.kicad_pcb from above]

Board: 2 copper layers, 364.3 x 135.7 mm, 230 parts (0 on the bottom side), 128 nets.

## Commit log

2026-02-13 Add kicad folder
2026-02-20 Removed J2 and cleaned up PCB a bit
    I realized that daughterboard support is useless as Void Switches are entirely contactless so there is no use in gasket mounting the keyboard.
2026-02-22 Fix issue where FB1 and F1 were in parallel
2026-03-04 Fix incorrect footprints for SW1 and SW2
